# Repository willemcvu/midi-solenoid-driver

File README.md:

# midi-solenoid-driver
A set of PCBs to drive solenoids using MIDI data, for use in automating musical instruments.

**The boards in this repo will be available for sale shortly on Tindie and/or eBay. If you are interested in buying assembled PCBs or bare PCBs, please send me a message as it would be helpful to know how many might sell. Thanks!**

The system consists of two parts: the solenoid driver board(s), and the USB interface board. The solenoid driver board(s) are daisy-chained via RJ12 ("phone cables"), and at the end of the chain is the USB interface board, which passes MIDI data from the USB port to all the solenoid driver boards (as many driver boards as are needed):

In addition to supporting daisy-chaining, the solenoid driver board has several notable features that allow for high usability with limited electronics experience.

Currently, MIDI data is fed to the solenoid drivers by a custom USB to serial-over-RJ12 board:

In the near future, more RJ12-compatible MIDI interface boards will be designed and released, allowing for more connectivity options. These will likely include:
 - Native plug-and-play USB MIDI (as opposed to the MIDI-over-serial in use right now)
 - Actual MIDI connector
 - Bluetooth adapter
 - AppleMIDI (RTP-MIDI / MIDI-over-network) WiFi interface

Additionally, more driver boards for devices other than solenoids will be designed/released, including a MIDI servo driver.

If you have specific needs for a particular project and need customized hardware, I can probably accomodate. Open an issue or contact me via my blog (https://willemhillier.wordpress.com/)and we'll go from there.

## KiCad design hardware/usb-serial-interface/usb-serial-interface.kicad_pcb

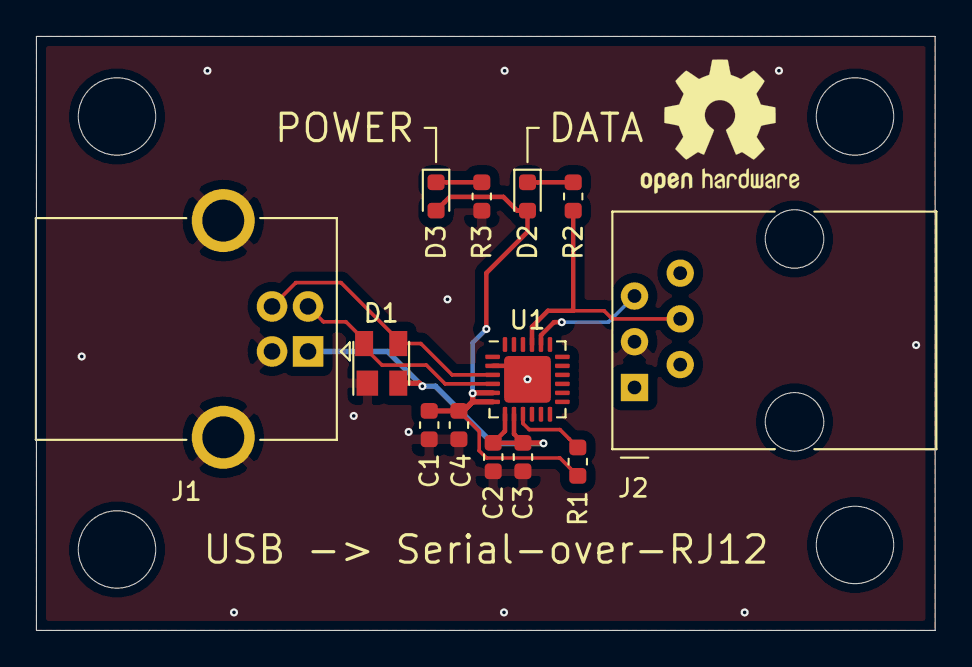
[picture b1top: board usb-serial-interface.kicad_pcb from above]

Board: 2 copper layers, 49.9 x 33.0 mm, 13 parts (0 on the bottom side), 10 nets.

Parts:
C1, C2: 4.7u; C_0603_1608Metric
C3, C4: 0.1u; C_0603_1608Metric
D1: SP0503BAHT; SOT-143
D2, D3: LED; LED_0603_1608Metric
J1: USB_B; USB_B_OST_USB-B1HSxx_Horizontal
J2: RJ12; RJ12_Amphenol_54601
R1: 4.7k; R_0603_1608Metric
R2, R3: 1k; R_0603_1608Metric
U1: CP2102N-A01-GQFN24; QFN-24-1EP_4x4mm_P0.5mm_EP2.6x2.6mm

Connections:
+3V3: C1.1, C4.1, D2.2, D3.2, R1.1, U1.5, U1.6
/D+: D1.3, J1.3, U1.3
/D-: D1.4, J1.2, U1.4
/RXD: J2.5, U1.20
/TXD: J2.4, R2.1, U1.21
GND: C1.2, C2.2, C3.2, C4.2, D1.1, J1.4, J1.5, J2.3, R3.1, U1.2, U1.25
unnamed: D2.1, R2.2
unnamed: D3.1, R3.2
unnamed: R1.2, U1.9
VBUS: C2.1, C3.1, D1.2, J1.1, U1.7, U1.8

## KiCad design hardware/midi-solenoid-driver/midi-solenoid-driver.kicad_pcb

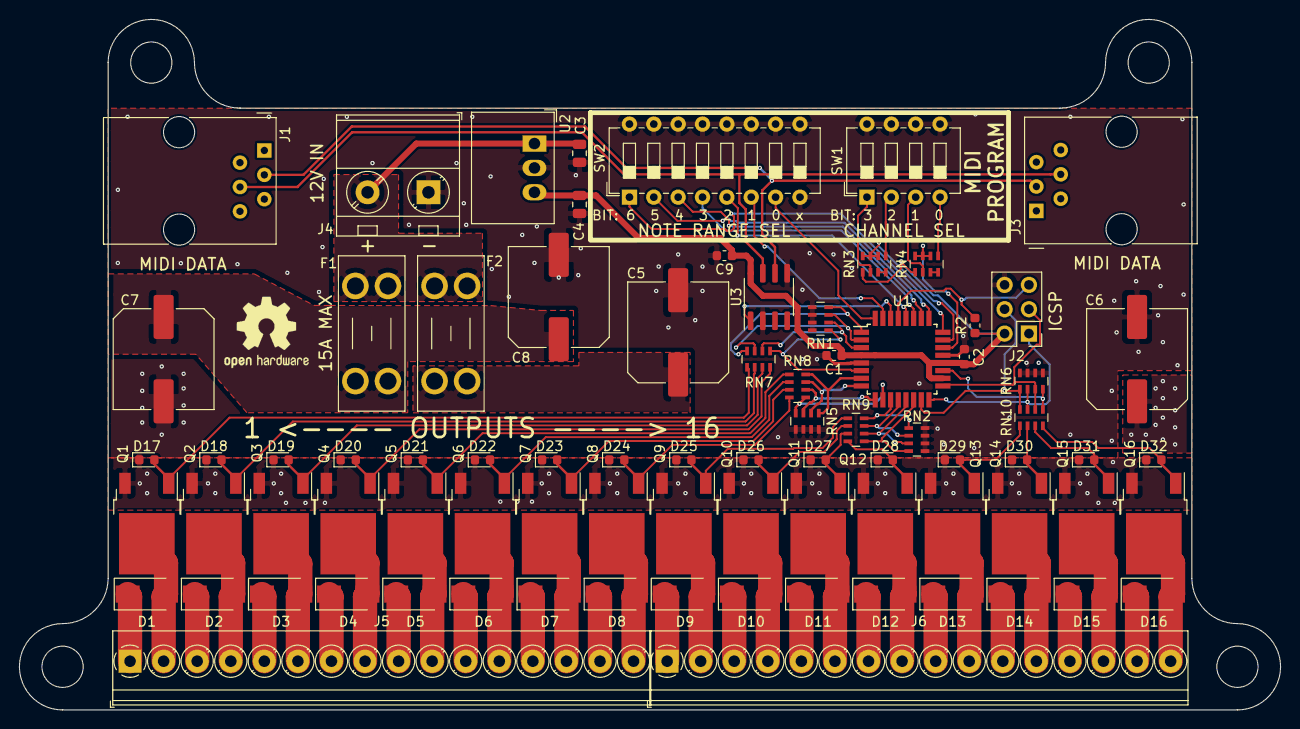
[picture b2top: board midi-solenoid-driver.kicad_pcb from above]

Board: 2 copper layers, 131.5 x 72.0 mm, 81 parts (0 on the bottom side), 72 nets.

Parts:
C1, C2, C9: 0.1uF; C_0603_1608Metric
C3, C4: 10uF; C_0805_2012Metric
C5, C6, C7, C8: 470; C_Elec_10x10.2
D1, D2, D3, D4, D5, D6, D7, D8, D9, D10, D11, D12, D13, D14, D15, D16: D_Small; D_SMA
D17, D18, D19, D20, D21, D22, D23, D24, D25, D26, D27, D28, D29, D30, D31, D32: LED_Small; LED_0603_1608Metric
F1, F2: 20A; Fuseholder_Blade_Mini_Keystone_3568
J1: LEFT_DATA; RJ12_Amphenol_54601
J2: Conn_02x03_Odd_Even; PinHeader_2x03_P2.54mm_Vertical
J3: RIGHT_DATA; RJ12_Amphenol_54601
J4: 12V_IN; TerminalBlock_MetzConnect_Type701_RT11L02HGLU_1x02_P6.35mm_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
J5: SOLENOIDS_OUT_1; TerminalBlock_Phoenix_PT-1,5-16-3.5-H_1x16_P3.50mm_Horizont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
J6: SOLENOIDS_OUT_2; TerminalBlock_Phoenix_PT-1,5-16-3.5-H_1x16_P3.50mm_Horizont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
Q1, Q2, Q3, Q4, Q5, Q6, Q7, Q8, Q9, Q10, Q11, Q12, Q13, Q14, Q15, Q16: Q_NMOS_GDS; TO-252-2
R2: 10k; R_0603_1608Metric
RN1, RN2, RN3, RN4, RN5, RN6: 10k; R_Array_Concave_4x0603
RN7, RN8, RN9, RN10: 1k; R_Array_Concave_4x0603
SW1: MIDI_CHANNEl; SW_DIP_SPSTx04_Slide_6.7x11.72mm_W7.62mm_P2.54mm_LowProfile
SW2: SW_DIP_x08; SW_DIP_SPSTx08_Slide_6.7x21.88mm_W7.62mm_P2.54mm_LowProfile
U1: ATmega328PB-AU; TQFP-32_7x7mm_P0.8mm
U2: R-78B5.0-2.0; Converter_DCDC_RECOM_R-78B-2.0_THT
U3: SN75LBC176D; SOIC-8_3.9x4.9mm_P1.27mm

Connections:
+5V: C1.1, C2.1, C4.1, C9.1, J2.2, R2.1, RN3.1, RN4.1, U1.4, U1.18, U1.20, U2.3, U3.8
+12V: C3.1, F1.2, F2.2, J4.2, U2.1
/12V_FUSED1: C7.1, C8.1, D1.1, D2.1, D3.1, D4.1, D5.1, D6.1, D7.1, D8.1, F1.1, J5.1, J5.3, J5.5, J5.7, J5.9, J5.11, J5.13, J5.15
/12V_FUSED2: C5.1, C6.1, D9.1, D10.1, D11.1, D12.1, D13.1, D14.1, D15.1, D16.1, F2.1, J6.1, J6.3, J6.5, J6.7, J6.9, J6.11, J6.13, J6.15
/CTRL1: RN1.4, RN7.8, U1.1
/CTRL2: RN1.3, RN7.7, U1.2
/CTRL3: RN1.2, RN7.6, U1.3
/CTRL4: RN1.1, RN7.5, U1.6
/CTRL5: RN5.1, RN8.8, U1.7
/CTRL6: RN5.2, RN8.7, U1.8
/CTRL7: RN5.3, RN8.6, U1.9
/CTRL8: RN5.4, RN8.5, U1.10
/CTRL9: RN2.1, RN9.8, U1.11
/CTRL10: RN2.2, RN9.7, U1.12
/CTRL11: RN2.3, RN9.6, U1.13
/CTRL12: RN2.4, RN9.5, U1.14
/CTRL13: J2.4, RN6.1, RN10.8, U1.15
/CTRL14: J2.1, RN6.2, RN10.7, U1.16
/CTRL15: J2.3, RN6.3, RN10.6, U1.17
/CTRL16: RN6.4, RN10.5, U1.19
/GATE1: D17.2, Q1.1, RN7.1
/GATE2: D18.2, Q2.1, RN7.2
/GATE3: D19.2, Q3.1, RN7.3
/GATE4: D20.2, Q4.1, RN7.4
/GATE5: D21.2, Q5.1, RN8.1
/GATE6: D22.2, Q6.1, RN8.2
/GATE7: D23.2, Q7.1, RN8.3
/GATE8: D24.2, Q8.1, RN8.4
/GATE9: D25.2, Q9.1, RN9.1
/GATE10: D26.2, Q10.1, RN9.2
/GATE11: D27.2, Q11.1, RN9.3
/GATE12: D28.2, Q12.1, RN9.4
/GATE13: D29.2, Q13.1, RN10.1
/GATE14: D30.2, Q14.1, RN10.2
/GATE15: D31.2, Q15.1, RN10.3
/GATE16: D32.2, Q16.1, RN10.4
/MIDI_CH_BIT0-1: RN3.6, RN3.7, RN3.8, U1.23
/MIDI_CH_BIT2-3: RN4.6, RN4.7, RN4.8, U1.22
/MIDI_IN: U1.30, U3.1
/MIDI_NOTE_BIT0: SW2.1, U1.24
/MIDI_NOTE_BIT1: SW2.2, U1.25
/MIDI_NOTE_BIT2: SW2.3, U1.26
/MIDI_NOTE_BIT3: SW2.4, U1.27
/MIDI_NOTE_BIT4: SW2.5, U1.28
/MIDI_NOTE_BIT5: SW2.6, U1.31
/MIDI_NOTE_BIT6: SW2.7, U1.32
/OUT1: D1.2, J5.2, Q1.2
/OUT2: D2.2, J5.4, Q2.2
/OUT3: D3.2, J5.6, Q3.2
/OUT4: D4.2, J5.8, Q4.2
/OUT5: D5.2, J5.10, Q5.2
/OUT6: D6.2, J5.12, Q6.2
/OUT7: D7.2, J5.14, Q7.2
/OUT8: D8.2, J5.16, Q8.2
/OUT9: D9.2, J6.2, Q9.2
/OUT10: D10.2, J6.4, Q10.2
/OUT11: D11.2, J6.6, Q11.2
/OUT12: D12.2, J6.8, Q12.2
/OUT13: D13.2, J6.10, Q13.2
/OUT14: D14.2, J6.12, Q14.2
/OUT15: D15.2, J6.14, Q15.2
/OUT16: D16.2, J6.16, Q16.2
/RESET: J2.5, R2.2, U1.29
/RS485_A: J1.3, J3.3, U3.6
/RS485_B: J1.4, J3.4, U3.7
GND: C1.2, C2.2, C3.2, C4.2, C5.2, C6.2, C7.2, C8.2, C9.2, D17.1, D18.1, D19.1, D20.1, D21.1, D22.1, D23.1, D24.1, D25.1, D26.1, D27.1, D28.1, D29.1, D30.1, D31.1, D32.1, J2.6, J4.1, Q1.3, Q2.3, Q3.3, Q4.3, Q5.3, Q6.3, Q7.3, Q8.3, Q9.3, Q10.3, Q11.3, Q12.3, Q13.3, Q14.3, Q15.3, Q16.3, RN1.5, RN1.6, RN1.7, RN1.8, RN2.5, RN2.6, RN2.7, RN2.8, RN5.5, RN5.6, RN5.7, RN5.8, RN6.5, RN6.6, RN6.7, RN6.8, SW1.5, SW1.6, SW1.7, SW1.8, SW2.8, SW2.9, SW2.10, SW2.11, SW2.12, SW2.13, SW2.14, SW2.15, SW2.16, U1.5, U1.21, U2.2, U3.2, U3.5
unnamed: RN3.2, SW1.1
unnamed: RN3.3, RN3.4
unnamed: RN3.5, SW1.2
unnamed: RN4.2, SW1.3
unnamed: RN4.3, RN4.4
unnamed: RN4.5, SW1.4

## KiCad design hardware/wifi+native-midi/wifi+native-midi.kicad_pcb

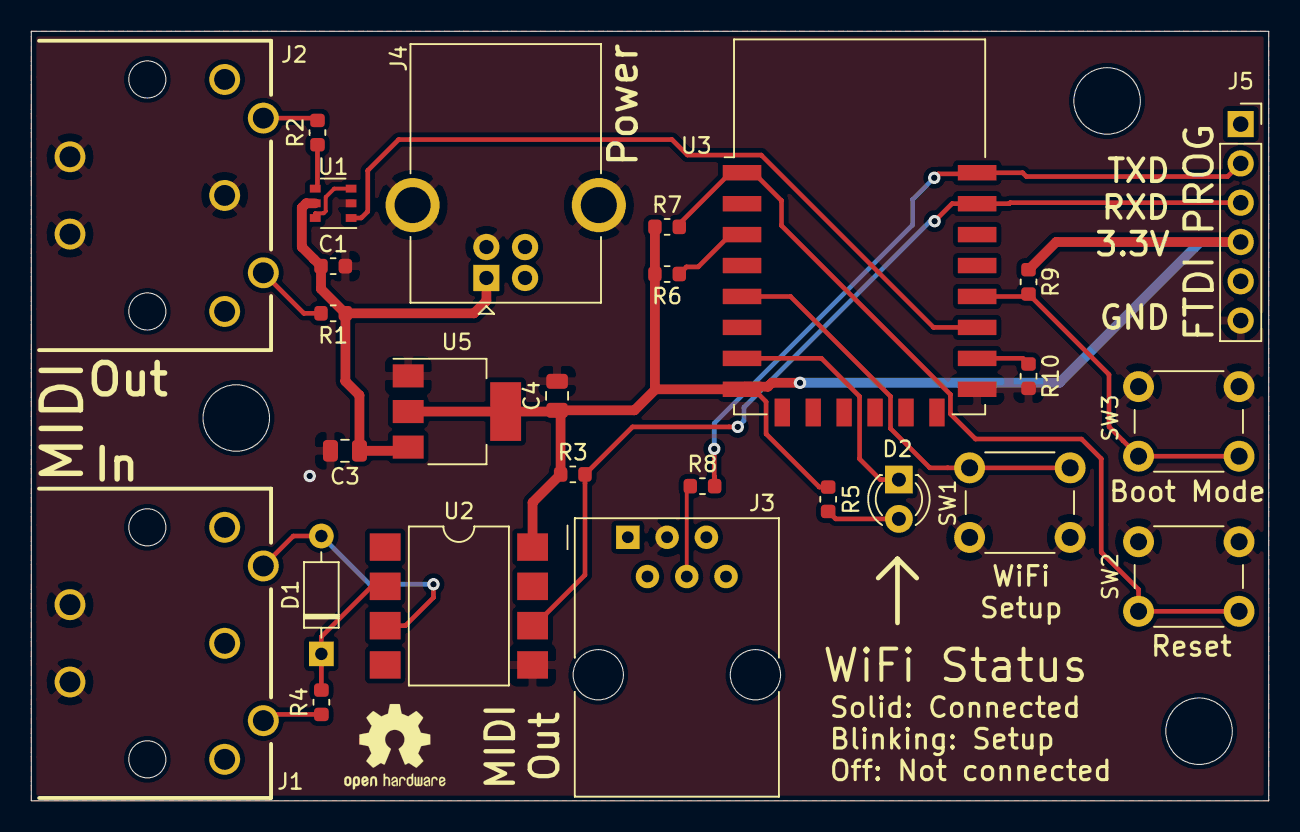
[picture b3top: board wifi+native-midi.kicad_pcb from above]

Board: 2 copper layers, 80.0 x 49.8 mm, 27 parts (0 on the bottom side), 21 nets.

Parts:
C1: 0.1u; C_0603_1608Metric
C3, C4: 10u; C_0805_2012Metric
D1: 1N914; D_DO-35_SOD27_P7.62mm_Horizontal
D2: LED; LED_D3.0mm
J1: MIDI_RX; 57PC5F_5_DIN_MIDI_GENERIC
J2: MIDI_TX; 57PC5F_5_DIN_MIDI_GENERIC
J3: 6P6C; RJ12_Amphenol_54601
J4: USB_B; USB_B_OST_USB-B1HSxx_Horizontal
J5: FTDI; PinSocket_1x06_P2.54mm_Vertical
R1, R2: 220; R_0603_1608Metric
R3: 470; R_0603_1608Metric
R4, R5: 1k; R_0603_1608Metric
R6, R7, R9, R10: 10k; R_0603_1608Metric
R8: 330; R_0603_1608Metric
SW1: WIFI_CONFIG; SW_PUSH_6mm_H9.5mm
SW2: RESET; SW_PUSH_6mm_H9.5mm
SW3: BOOT_MODE; SW_PUSH_6mm_H9.5mm
U1: 74HC2G04; TSOP-6_1.65x3.05mm_P0.95mm
U2: 6N138; SMDIP-8_W9.53mm
U3: ESP-12F; ESP-12E
U5: AZ1117-3.3; SOT-223-3_TabPin2

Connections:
+3V3: C4.1, J5.4, R3.1, R5.1, R6.2, R7.1, R9.1, U2.8, U3.8, U5.2
+5V: C1.1, C3.1, J4.1, R1.1, U1.5, U5.3
/GPIO0: R9.2, SW3.2, U3.18
/MIDI_IN: J5.3, R3.2, U2.6, U3.21
/MIDI_OUT: U1.1, U3.17
/RJ12_MIDI_OUT: J5.2, R8.2, U3.22
/RST: R7.2, SW2.2, U3.1
/WIFI_CONFIG: SW1.1, U3.5
/WIFI_STATUS: D2.1, U3.7
GND: C1.2, C3.2, C4.2, J1.GND, J2.2, J2.GND, J3.3, J4.4, J4.5, J5.6, R10.2, SW1.2, SW2.1, SW3.1, U1.2, U2.5, U3.15, U5.1
unnamed: D1.1, R4.2, U2.2
unnamed: D1.2, J1.5, U2.3
unnamed: D2.2, R5.2
unnamed: J1.4, R4.1
unnamed: J2.4, R1.2
unnamed: J2.5, R2.2
unnamed: J3.4, R8.1
unnamed: R2.1, U1.4
unnamed: R6.1, U3.3
unnamed: R10.1, U3.16
unnamed: U1.3, U1.6

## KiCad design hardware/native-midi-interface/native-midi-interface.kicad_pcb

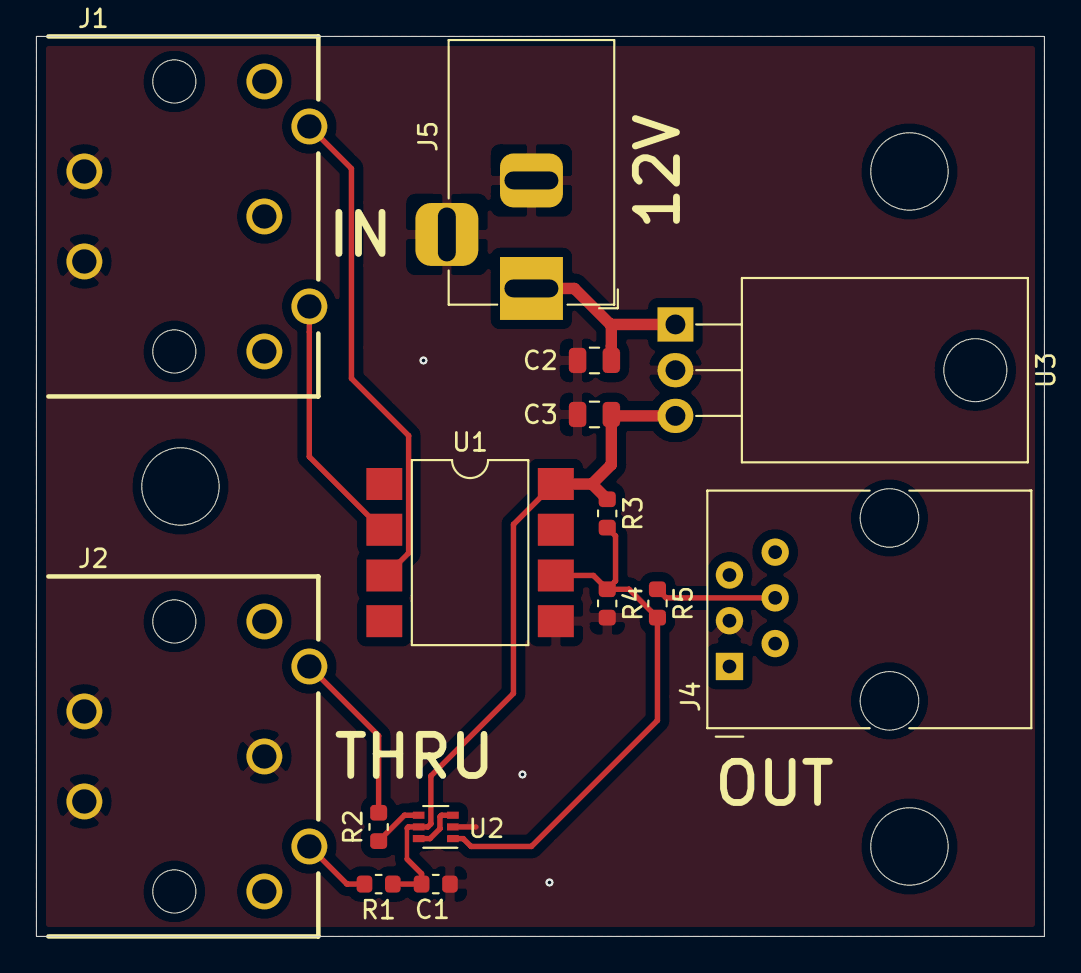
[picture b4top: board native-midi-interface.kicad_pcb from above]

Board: 2 copper layers, 56.0 x 50.0 mm, 15 parts (0 on the bottom side), 11 nets.

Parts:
C1: 1u; C_0603_1608Metric
C2, C3: 10u; C_0805_2012Metric
J1: MIDI_RX; 57PC5F_5_DIN_MIDI_GENERIC
J2: MIDI_PASSTHROUGH; 57PC5F_5_DIN_MIDI_GENERIC
J4: 6P6C; RJ12_Amphenol_54601
J5: BARREL_JACK_12V; BarrelJack_Horizontal
R1, R2: 220; R_0603_1608Metric
R3: 470; R_0603_1608Metric
R4: 1k; R_0603_1608Metric
R5: 330; R_0603_1608Metric
U1: 6N138; SMDIP-8_W9.53mm
U2: 74HC2G04; SOT-363_SC-70-6
U3: L7805; TO-220-3_Horizontal_TabDown

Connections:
+5V: C1.1, C3.1, R1.1, R3.1, U1.8, U2.5, U3.3
+12V: C2.1, J5.1, U3.1
/MIDI_UART: R3.2, R4.1, R5.2, U1.6, U2.1
GND: C1.2, C2.2, C3.2, J1.GND, J2.2, J2.GND, J4.3, J5.2, J5.3, R4.2, U1.5, U2.2, U3.2
unnamed: J1.4, U1.2
unnamed: J1.5, U1.3
unnamed: J2.4, R1.2
unnamed: J2.5, R2.2
unnamed: J4.4, R5.1
unnamed: R2.1, U2.4
unnamed: U2.3, U2.6

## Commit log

2019-07-27 Schematic done
2019-07-28 mostly finished PCB layout
    Done w/ all but reference designators and silkscreen cleanup
2019-07-28 PCB mostly done.
2019-07-29 USB interface schematic done
2019-07-29 USB to serial board done
    - Finished laying out
    - Added RX line to RJ12 for potential future use
    - Made gerbers
2019-07-29 Added OSHW logo to driver board
    - Added logo
    - Made new gerbers
2019-07-29 Removed thermal reliefs on high-current pins + made new gerbers
2019-07-30 Added solenoid driver board renders + diagram
2019-07-30 Made multi-board layout pic
2019-07-30 Added more info about USB interface board
2019-07-30 Added pics of USB interface board
2019-07-30 Updated USB interface terminology
2019-08-02 Made native midi interface
    TODO: Update readme to reflect the existance of this board
2019-08-11 Made v2 of serial interface + panelized
2019-08-11 Firmware mostly written
2019-08-11 Made iBoms
2019-08-11 Made v1.1 of driver board + gerbers
    - Added thermal relief to difficult-to-solder pads
    - Updated silkscreen
2019-08-11 Fixed gerber locations
2019-08-11 made schematic for wifi-native-midi
2019-08-11 Shipping wifi+native-midi
2019-08-12 Update wifi+native-midi_panelized.kicad_pcb
    Updated panelized version
2019-08-14 AddedRS485 transceiver, need to ship new rev
2019-08-16 Lowest MIDI note selection via DIP switchesa now works properly
2019-08-21 Channel assignment via DIP switches now works properly
2019-08-26 New USB to serial board image
2019-09-16 Initial commit of wifi-native-midi firmware. Not working.
2019-09-16 RJ12 output works.
2019-09-16 Wifi-manager integration, mostly untested
2019-09-26 wifi-native-midi now builds via platformio
2019-10-01 Test commit for EE106
2020-08-28 new usb serial gerbers
2020-10-02 Fix potential array index out of bounds error
2020-10-02 Fix note 0 bug
    When the Note Range Selection dip switches were set to 0, it was impossible to activate the first mosfet, (Q1 / note 0 in this configuration)
